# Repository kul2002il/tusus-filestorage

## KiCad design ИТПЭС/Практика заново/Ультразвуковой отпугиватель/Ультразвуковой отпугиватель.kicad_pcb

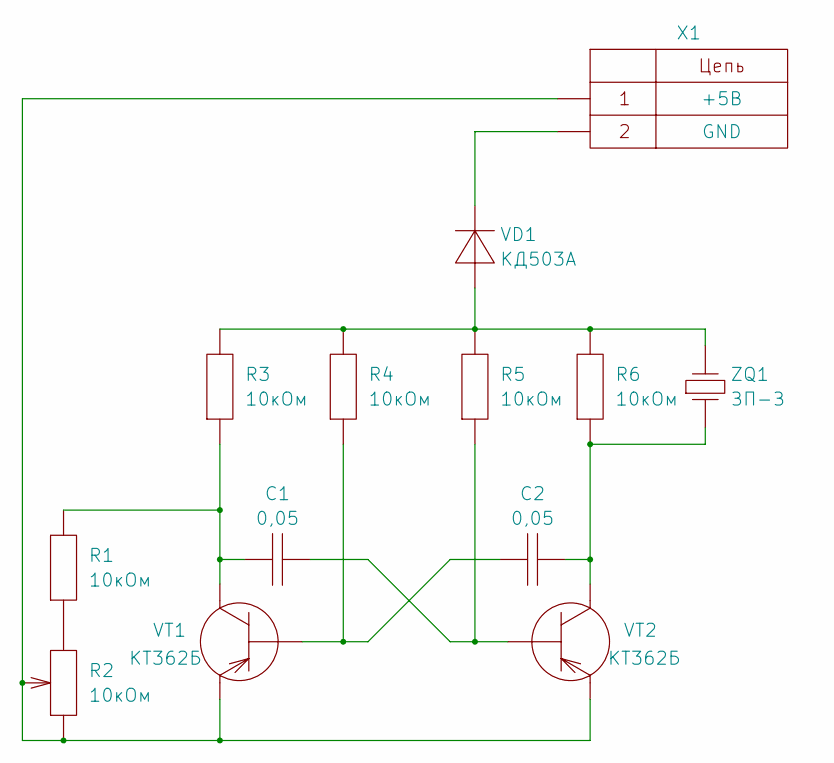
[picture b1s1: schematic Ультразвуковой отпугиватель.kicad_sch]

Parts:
C1, C2: 0,05; C_Disc_D7.5mm_W2.5mm_P5.00mm
R1, R3, R4, R5, R6: 10кОм; R_Axial_DIN0207_L6.3mm_D2.5mm_P10.16mm_Horizontal
R2: 10кОм; Potentiometer_Bourns_3296W_Vertical
VD1: КД503А; D_DO-15_P15.24mm_Horizontal
VT1, VT2: КТ362Б; TO-92_Inline
X1: CONN_2; BarrelJack_GCT_DCJ200-10-A_Horizontal
ZQ1: ЗП-З; Buzzer_15x7.5RM7.6

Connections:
unnamed: R1.1, R2.3
unnamed: R3.2, R4.2, R5.2, R6.2, VD1.2 (A), ZQ1.2
unnamed: VD1.1 (K), X1.2
unnamed: C2.1, R4.1, VT1.1 (B)
unnamed: C1.1, R1.2, R3.1, VT1.2 (C)
unnamed: R2.1, R2.2, VT1.3 (E), VT2.3 (E), X1.1
unnamed: C1.2, R5.1, VT2.1 (B)
unnamed: C2.2, R6.1, VT2.2 (C), ZQ1.1

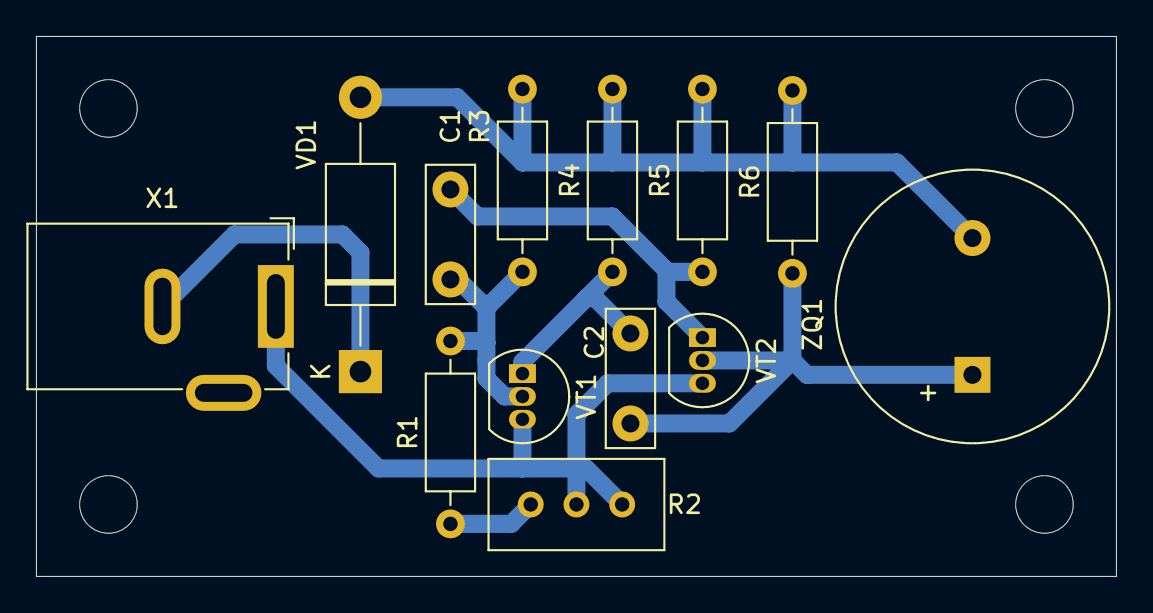
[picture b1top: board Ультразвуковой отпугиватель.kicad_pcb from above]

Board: 2 copper layers, 60.0 x 30.0 mm, 13 parts (0 on the bottom side), 8 nets.

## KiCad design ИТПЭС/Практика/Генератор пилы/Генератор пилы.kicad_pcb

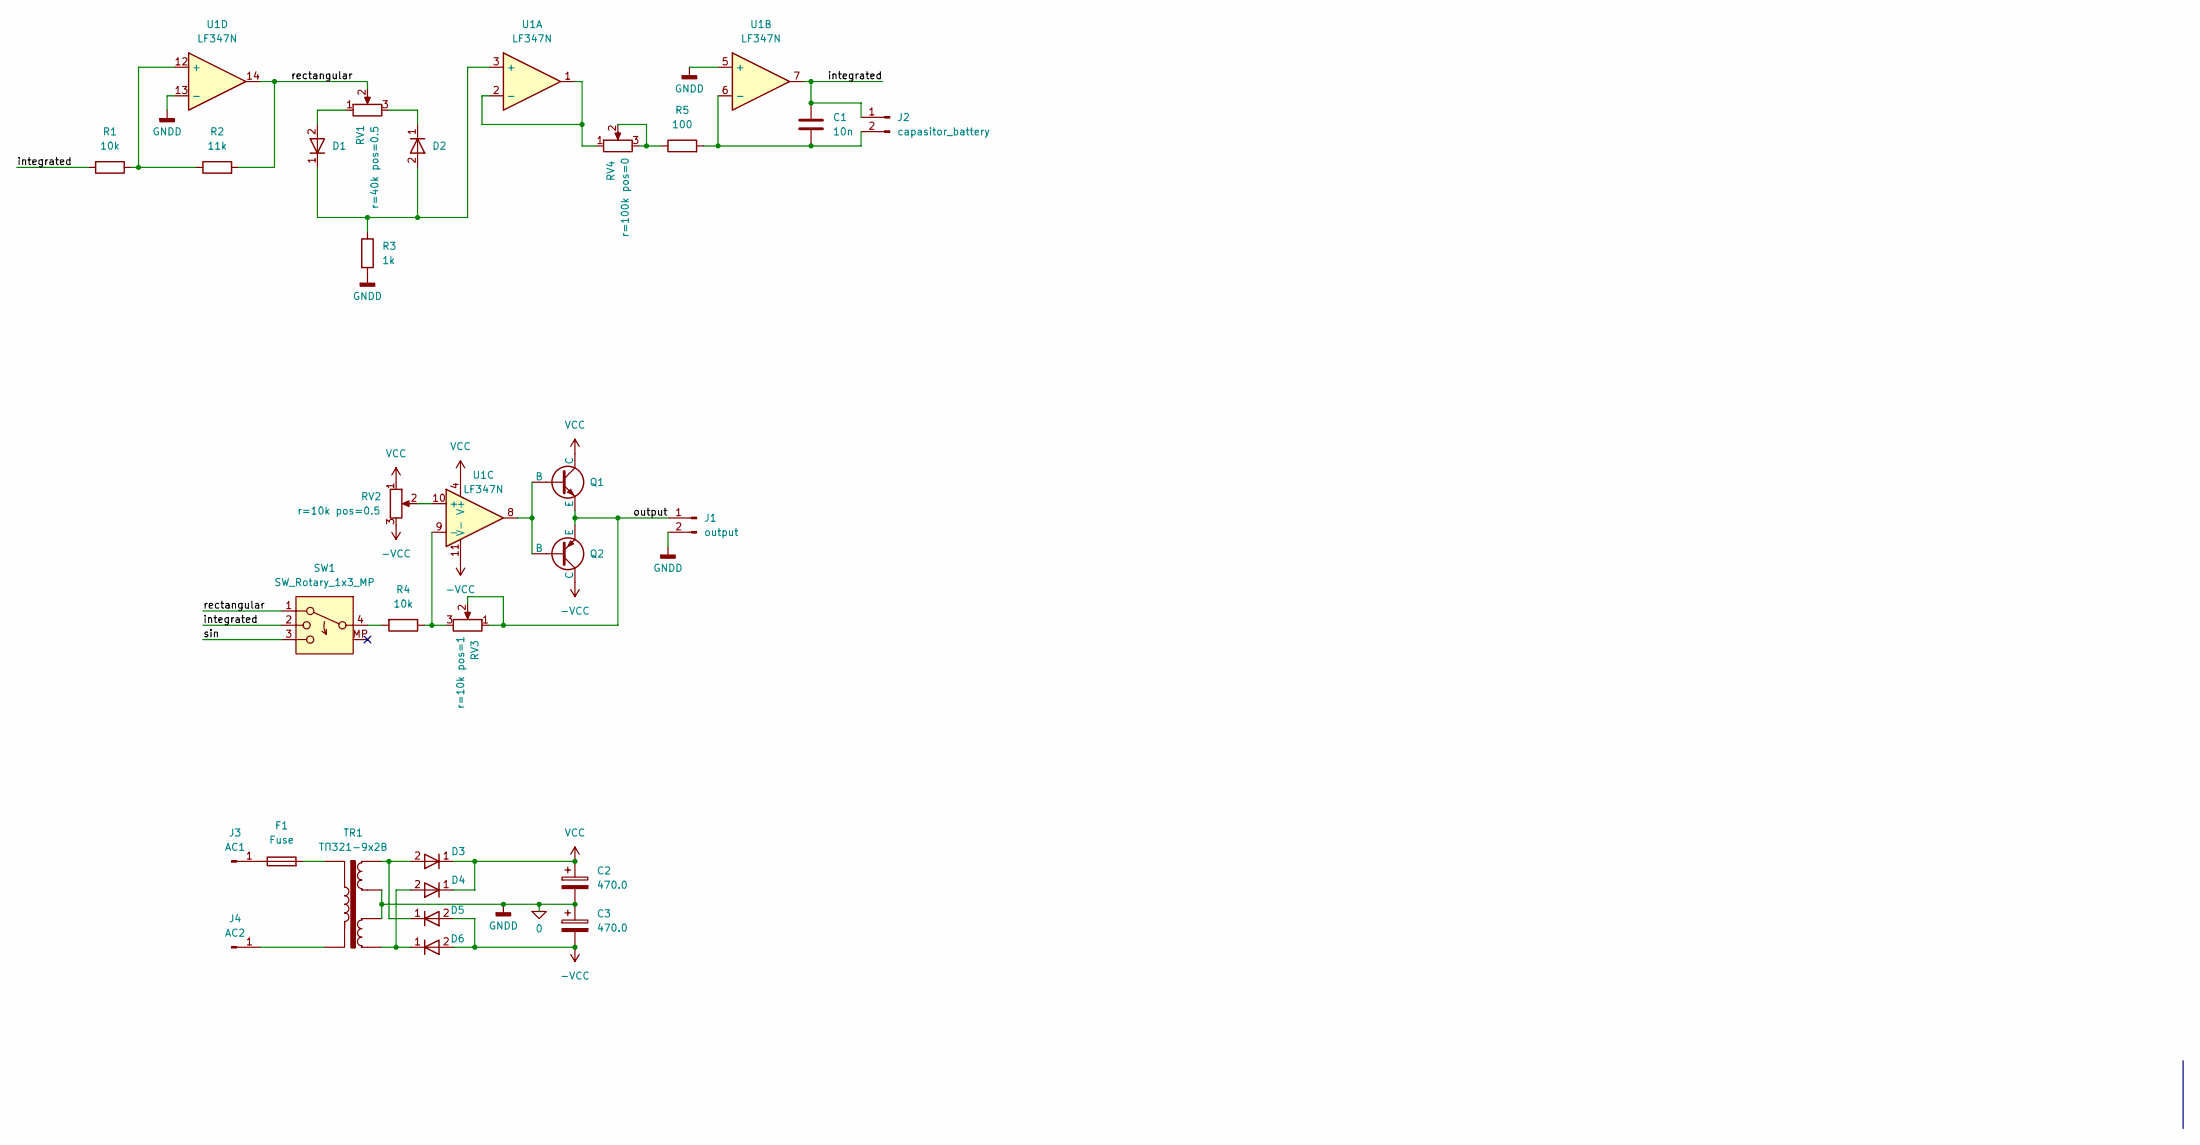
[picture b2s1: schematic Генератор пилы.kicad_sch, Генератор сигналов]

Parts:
C1: 10n; C_Radial_D8.0mm_H7.0mm_P3.50mm
C2, C3: 470.0; CP_Radial_D8.0mm_P3.80mm
D1, D2: D; D_DO-35_SOD27_P7.62mm_Horizontal
D3, D4, D5, D6: D; D_DO-41_SOD81_P12.70mm_Horizontal
F1: Fuse; Fuseholder_Littelfuse_100_series_5x20mm
J1: output; PinHeader_1x02_P2.54mm_Vertical
J2: capasitor_battery; PinHeader_1x02_P2.54mm_Vertical
J3: AC1; SolderWire-1.5sqmm_1x01_D1.7mm_OD3.9mm
J4: AC2; SolderWire-1.5sqmm_1x01_D1.7mm_OD3.9mm
Q1: NPN; TO-92_Inline_Wide
Q2: PNP; TO-92_Inline_Wide
R1, R4: 10k; R_Axial_DIN0309_L9.0mm_D3.2mm_P12.70mm_Horizontal
R2: 11k; R_Axial_DIN0309_L9.0mm_D3.2mm_P12.70mm_Horizontal
R3: 1k; R_Axial_DIN0309_L9.0mm_D3.2mm_P12.70mm_Horizontal
R5: 100; R_Axial_DIN0309_L9.0mm_D3.2mm_P12.70mm_Horizontal
RV1: 40k; Potentiometer_Alps_RK163_Single_Horizontal
RV2, RV3: 10k; Potentiometer_Alps_RK163_Single_Horizontal
RV4: 100k; Potentiometer_Alps_RK163_Single_Horizontal
SW1: SW_Rotary_1x3_MP; PinHeader_1x04_P2.54mm_Vertical
TR1: ТП321-9х2В; ТП321-9_2В
U1: LF347N; DIP-14_W7.62mm

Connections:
0: C2.2, C3.1, J1.2, R3.2, TR1.4, TR1.5, U1.5 (+), U1.13 (-)
-VCC: C3.2, D5.2 (A), D6.2 (A), Q2.1 (C), RV2.3, U1.11 (V-)
/integrated: C1.1, J2.1, R1.2, SW1.2, U1.7
/output: J1.1, Q1.3 (E), Q2.3 (E), RV3.1, RV3.2
/rectangular: R2.2, RV1.2, SW1.1, U1.14
/sin: SW1.3
unnamed: D1.2 (A), RV1.1
unnamed: D1.1 (K), D2.2 (A), R3.1, U1.3 (+)
unnamed: D2.1 (K), RV1.3
unnamed: D3.2 (A), D5.1 (K), TR1.3
unnamed: D4.2 (A), D6.1 (K), TR1.6
unnamed: F1.2, TR1.1
unnamed: C1.2, J2.2, R5.2, U1.6 (-)
unnamed: F1.1, J3.1
unnamed: J4.1, TR1.2
unnamed: Q1.2 (B), Q2.2 (B), U1.8
unnamed: R4.2, SW1.4
unnamed: R5.1, RV4.2, RV4.3
unnamed: RV4.1, U1.1, U1.2 (-)
unnamed: RV2.2, U1.10 (+)
unnamed: R4.1, RV3.3, U1.9 (-)
unnamed: R1.1, R2.1, U1.12 (+)
VCC: C2.1, D3.1 (K), D4.1 (K), Q1.1 (C), RV2.1, U1.4 (V+)

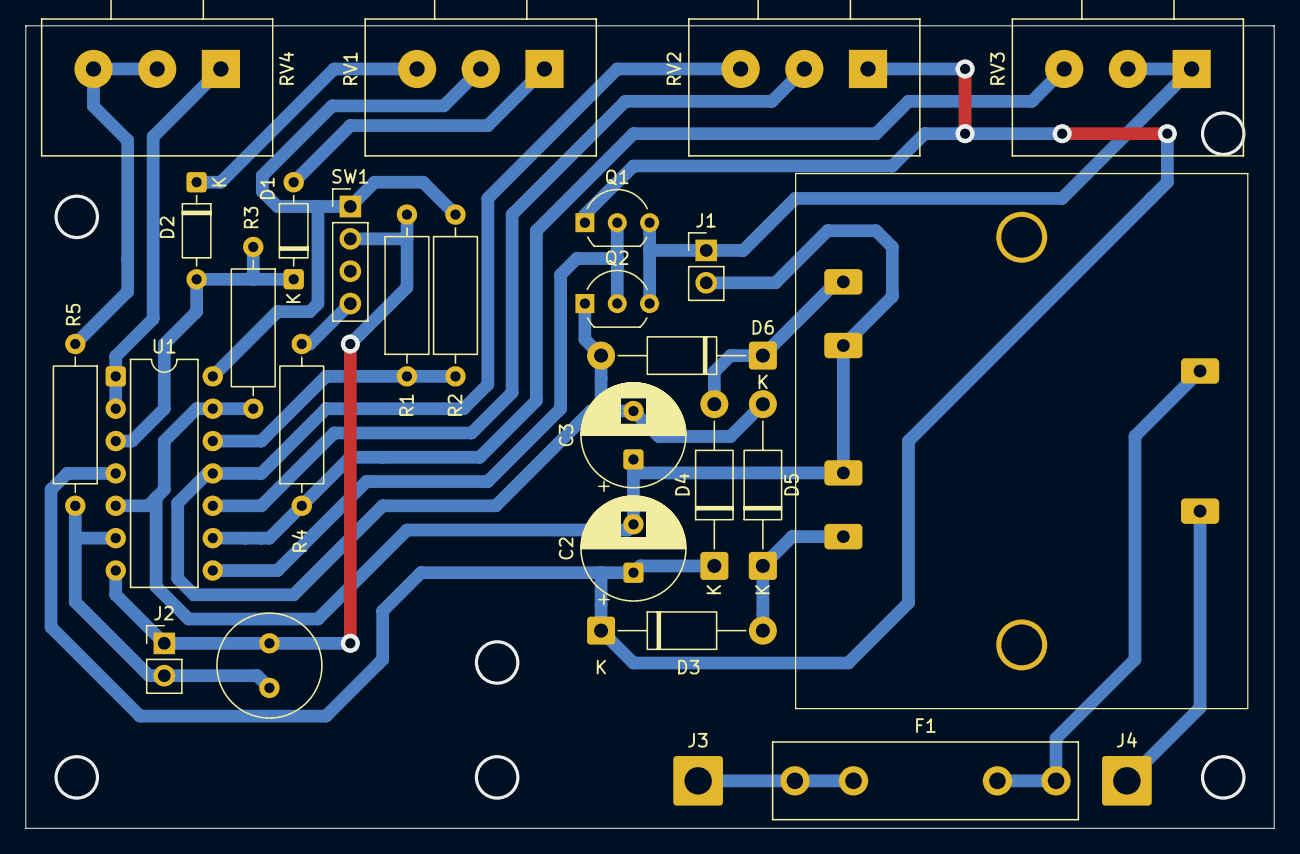
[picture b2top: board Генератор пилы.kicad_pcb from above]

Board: 2 copper layers, 98.0 x 63.0 mm, 28 parts (0 on the bottom side), 22 nets.
